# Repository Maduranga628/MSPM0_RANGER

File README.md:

# MSPM0_RANGER
Custom Development Board Using Texas Instruments' MSPM0 MCU.

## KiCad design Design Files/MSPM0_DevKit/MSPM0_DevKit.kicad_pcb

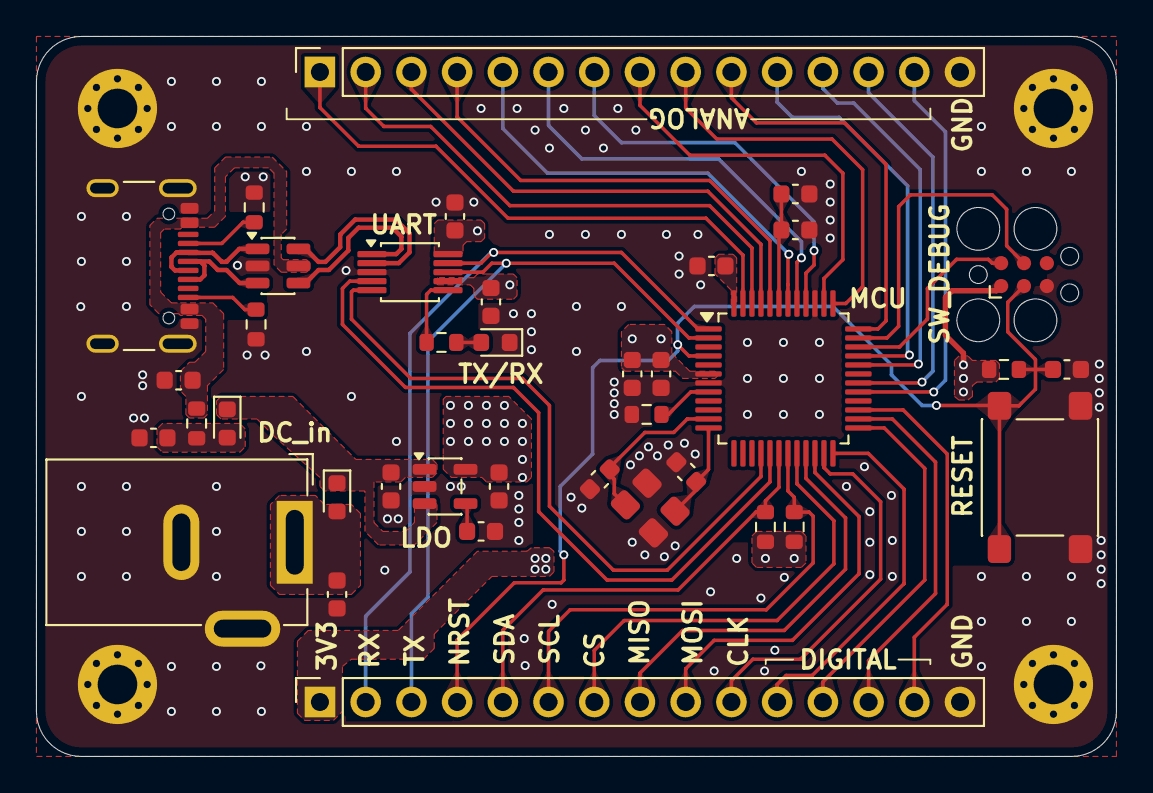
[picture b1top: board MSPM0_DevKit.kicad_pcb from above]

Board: 4 copper layers, 60.0 x 40.0 mm, 42 parts (0 on the bottom side), 51 nets.

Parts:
C1, C6: 10n; C_0603_1608Metric
C2, C11, C12, C14: 10u; C_0603_1608Metric
C3, C4, C5, C9, C10, C13, C15, C16: 470n; C_0603_1608Metric
C7, C8: 15p; C_0603_1608Metric
D1, D2: CDBU70-HF; D_0603_1608Metric
DC_in: Barrel_Jack; BarrelJack_GCT_DCJ200-10-A_Horizontal
J1: USB_C; USB_C_Receptacle_GCT_USB4105-xx-A_16P_TopMnt_Horizontal
J4, J5: Conn_01x15_Pin; PinSocket_1x15_P2.54mm_Vertical
LDO: SPX3819M5-L-3-3; SOT-23-5
MCU: MSPM0G3507SPTR; LQFP-48_7x7mm_P0.5mm
MH1, MH2, MH3, MH4: MountingHole_Pad; MountingHole_2.2mm_M2_Pad_Via
R1: 47k; R_0603_1608Metric
R2: 100k; R_0603_1608Metric
R3: 0R; R_0603_1608Metric
R4, R5, R7, R8: 5k1; R_0603_1608Metric
R6: 1k; R_0603_1608Metric
RESET: RST_SW; SW_SPST_PTS645Sx43SMTR92
SW_DEBUG: SW_Debug; Tag-Connect_TC2030-IDC-FP_2x03_P1.27mm_Vertical
TX/RX: LED; LED_0603_1608Metric
U2: USBLC6-2SC6; SOT-23-6
UART: CH340E; MSOP-10_3x3mm_P0.5mm
Y1: 8MHz; Crystal_SMD_3225-4Pin_3.2x2.5mm

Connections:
+1V35: C3.1, MCU.48 (VCORE)
+3V3: C1.1, C2.1, C14.1, C15.1, C16.1, J4.1, LDO.5 (OUT), MCU.6 (VDD), R1.1, R7.2, R8.2, SW_DEBUG.1 (VCC), UART.7 (VCC), UART.10 (V3)
+5V: C12.1, D1.1 (K), D2.1 (K), LDO.1 (IN), LDO.3 (EN)
+VBUS: C9.1, J1.A4 (VBUS), J1.A9 (VBUS), J1.B4 (VBUS), J1.B9 (VBUS), R3.1, U2.5 (VBUS)
+VBUSF: C10.1, D1.2 (A), R3.2
+VCC: C11.1, D2.2 (A), DC_in.1
/BP_LDO: C13.1, LDO.4 (BP)
/CC1: J1.A5 (CC1), R5.2
/CC2: J1.B5 (CC2), R4.2
/CLK_IN: C7.1, MCU.11 (PA5_/_HFXIN_/_FCC_IN), Y1.3
/CLK_OUT: C8.1, MCU.12 (PA6_/_HFCLK_IN_/_HFXOUT), Y1.1
/NRST: C6.1, J4.4, MCU.4 (NRST), R1.2, RESET.1, SW_DEBUG.3 (~RESET)
/PA12: J4.14, MCU.27 (PA12_/_FCC_IN)
/PA14: J5.14, MCU.29 (PA14_/_CLK_OUT_/A0_12)
/PA15: J5.13, MCU.30 (PA15_/_A1_0)
/PA17: J5.12, MCU.32 (PA17_/_A1_2)
/PA18: J5.11, MCU.33 (PA18_/_A1_3)
/PA22: J5.7, MCU.40 (PA22_/_CLK_OUT_/_A0_7)
/PA24: J5.4, MCU.44 (PA24_/_A0_3)
/PA25: J5.3, MCU.45 (PA25_/_A0_2_/_OPA0_IN1+)
/PA26: J5.2, MCU.46 (PA26_/_A0_1)
/PA27: J5.1, MCU.47 (PA27_/_RTC_OUT_/_A0_0)
/PB14: J4.11, MCU.24 (PB14)
/PB15: J4.12, MCU.25 (PB15)
/PB16: J4.13, MCU.26 (PB16)
/PB17: J5.10, MCU.36 (PB17_/_A1_4)
/PB18: J5.9, MCU.37 (PB18_/_A1_5)
/PB19: J5.8, MCU.38 (PB19_/_A1_6)
/PB20: J5.6, MCU.41 (PB20_/_A0_6)
/PB24: J5.5, MCU.42 (PB24_/_A0_5)
/ROSC: MCU.8 (PA2_/_ROSC), R2.2
/SCL: J4.6, MCU.19 (PA11), R8.1
/SDA: J4.5, MCU.18 (PA10_/_CLK_OUT), R7.1
/SPI1_CLK: J4.10, MCU.23 (PB9)
/SPI1_CS: J4.7, MCU.20 (PB6)
/SPI1_MISO: J4.8, MCU.21 (PB7)
/SPI1_MOSI: J4.9, MCU.22 (PB8)
/SWCLK: MCU.35 (PA20_/_SWCLK), SW_DEBUG.4 (SWCLK)
/SWDIO: MCU.34 (PA19_/_SWDIO), SW_DEBUG.2 (SWDIO)
/TNO_IC: R6.2, UART.6 (TNOW)
/TNO_LED: R6.1, TX/RX.2 (A)
/UART0_CTS: MCU.17 (PA9_/_RTC_OUT/_CLK_OUT), UART.4 (~RTS)
/UART0_RTS: MCU.16 (PA8), UART.5 (~CTS)
/UART0_RX: J4.3, MCU.2 (PA1), UART.8 (TXD)
/UART0_TX: J4.2, MCU.1 (PA0), UART.9 (RXD)
/USB+: U2.4 (I/O2), UART.1 (UD+)
/USB-: U2.6 (I/O1), UART.2 (UD-)
/USBD+: J1.A6 (D+), J1.B6 (D+), U2.3 (I/O2)
/USBD-: J1.A7 (D-), J1.B7 (D-), U2.1 (I/O1)
/VREF+: C4.1, C5.1, MCU.43 (PA23_/_VREF+)
GND: C1.2, C2.2, C3.2, C4.2, C5.2, C6.2, C7.2, C8.2, C9.2, C10.2, C11.2, C12.2, C13.2, C14.2, C15.2, C16.2, DC_in.2, DC_in.3, J1.A1 (GND), J1.A12 (GND), J1.B1 (GND), J1.B12 (GND), J1.S1 (SHIELD), J4.15, J5.15, LDO.2 (GND), MCU.7 (VSS), MCU.39 (PA21_/_A1_7_/_VREF-), MH1.1, MH2.1, MH3.1, MH4.1, R2.1, R4.1, R5.1, RESET.2, SW_DEBUG.5 (GND), TX/RX.1 (K), U2.2 (GND), UART.3 (GND), Y1.2, Y1.4

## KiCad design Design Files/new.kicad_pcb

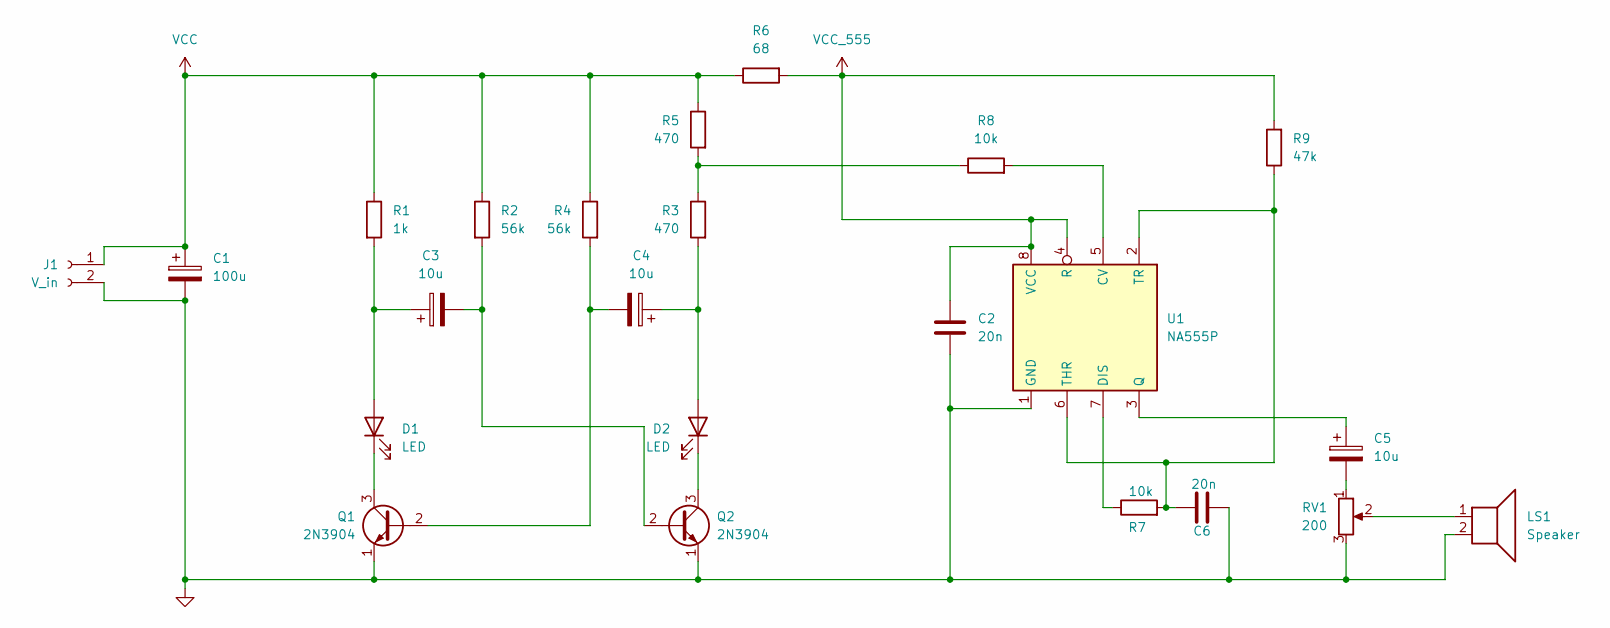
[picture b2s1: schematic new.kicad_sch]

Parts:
C1: 100u; C_Radial_D6.3mm_H11.0mm_P2.50mm
C2, C6: 20n; C_Disc_D4.3mm_W1.9mm_P5.00mm
C3, C4, C5: 10u; C_Radial_D6.3mm_H11.0mm_P2.50mm
D1, D2: LED; LED_D3.0mm
J1: V_in; PinSocket_1x02_P2.54mm_Vertical
LS1: Speaker; PinSocket_1x02_P2.54mm_Vertical
Q1, Q2: 2N3904; TO-92_Inline
R1: 1k; R_Axial_DIN0207_L6.3mm_D2.5mm_P7.62mm_Horizontal
R2, R4: 56k; R_Axial_DIN0207_L6.3mm_D2.5mm_P7.62mm_Horizontal
R3, R5: 470; R_Axial_DIN0207_L6.3mm_D2.5mm_P7.62mm_Horizontal
R6: 68; R_Axial_DIN0207_L6.3mm_D2.5mm_P7.62mm_Horizontal
R7, R8: 10k; R_Axial_DIN0207_L6.3mm_D2.5mm_P7.62mm_Horizontal
R9: 47k; R_Axial_DIN0207_L6.3mm_D2.5mm_P7.62mm_Horizontal
RV1: 200; Potentiometer_ACP_CA9-H5_Horizontal
U1: NA555P; DIP-8_W7.62mm

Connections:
GND: C1.2, C2.2, C6.2, J1.2, LS1.2, Q1.1 (E), Q2.1 (E), RV1.3, U1.1 (GND)
unnamed: C5.2, RV1.1
unnamed: C3.1, D1.2 (A), R1.2
unnamed: D1.1 (K), Q1.3 (C)
unnamed: C4.1, D2.2 (A), R3.2
unnamed: D2.1 (K), Q2.3 (C)
unnamed: LS1.1, RV1.2
unnamed: C4.2, Q1.2 (B), R4.2
unnamed: C3.2, Q2.2 (B), R2.2
unnamed: R3.1, R5.2, R8.1
unnamed: R8.2, U1.5 (CV)
unnamed: R7.1, U1.7 (DIS)
unnamed: C5.1, U1.3 (Q)
unnamed: C6.1, R7.2, R9.1, U1.2 (TR), U1.6 (THR)
VCC: C1.1, J1.1, R1.1, R2.1, R4.1, R5.1, R6.1
VCC_555: C2.1, R6.2, R9.2, U1.4 (R), U1.8 (VCC)

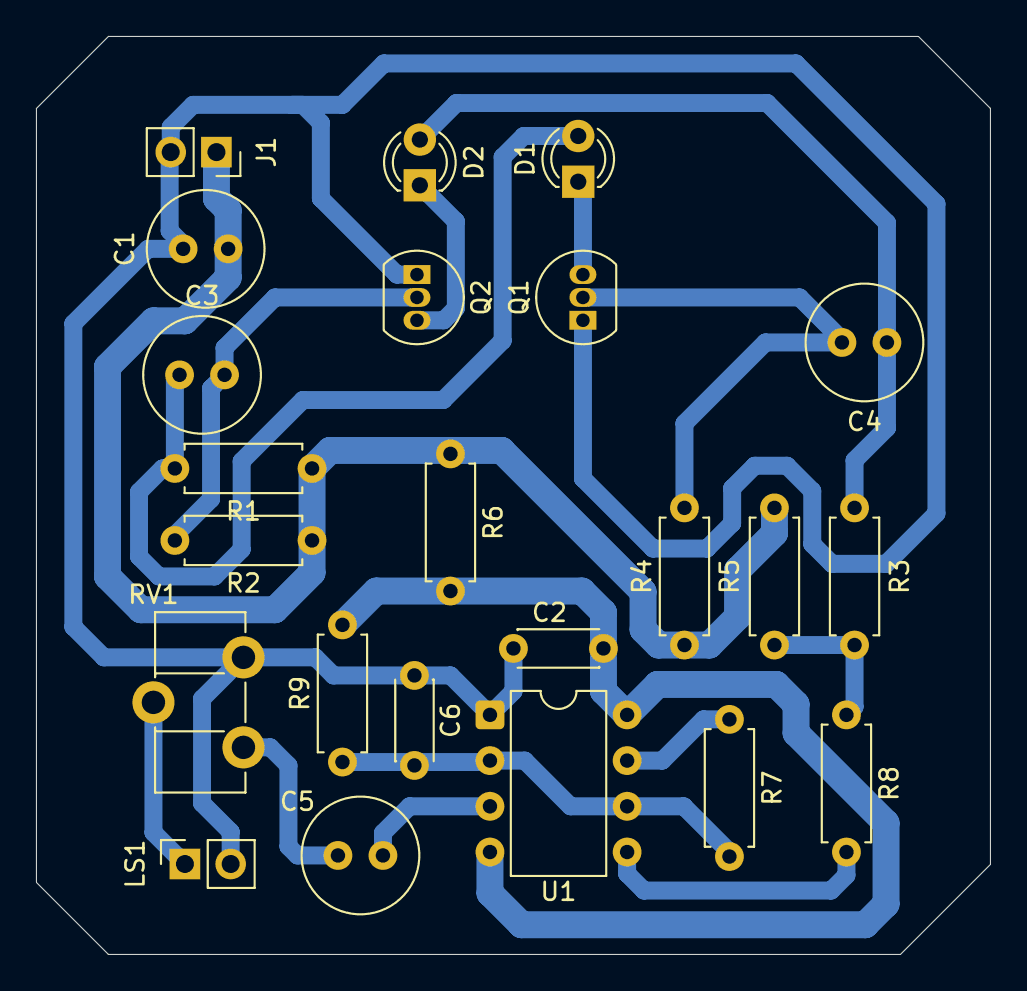
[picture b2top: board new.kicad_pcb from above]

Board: 2 copper layers, 53.0 x 51.0 mm, 23 parts (0 on the bottom side), 16 nets.

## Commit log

2025-12-01 Add files via upload
    KiCAD files for the design.
2025-12-01 Add files via upload
    Schematics, 2D PCB and 3D views of the PCB
2025-12-01 Rename MSPM0_DevKit.pdf to MSPM0_DevKit_Schematic.pdf
2025-12-11 Create temp
